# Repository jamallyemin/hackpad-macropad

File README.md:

# hackpad-macropad :3

very kewl 3-key macropad made for hack club hackpad! 

it's a compact custom macropad featuring a rotary encoder, 0.91" OLED screen, WS2812B RGB LED, and a piezo buzzer for cool noises/audio feedback. everything is powered by the Seeed Studio XIAO RP2040 placed right at the top of the board!

## pics !!

### schematic

### 3d case

### pcb layout

### kicad pcb layout

## features !!
* **Seeed XIAO RP2040:** mounted at the top of the PCB for clean USB-C access.
* **3x MX Switches:** mechanical key switches for your daily macros/shortcuts.
* **EC11 Rotary Encoder:** smooth knob control for volume, scrolling, or custom bindings (with built-in push button!).
* **0.91" I2C OLED Display:** 128x32 screen to show custom animations, status info, or graphics.
* **WS2812B RGB LED:** addressable Neopixel for custom lighting effects.
* **Piezo Buzzer:** self-supplied buzzer for playin chiptunes or audio feedback!

## repo structure

* `/PCB` - KiCad schematic (`.kicad_sch`), PCB layout (`.kicad_pcb`), and project files.
* `/CAD` - 3D model STEP files (`hackpad.step`).
* `/production` - Gerber files (`gerbers.zip`), 3D printable STL files (`Top.stl`, `Bottom.stl`), and production code.
* `/images` - Screenshots and 3D preview renders.
* `/Firmware` - CircuitPython code (`main.py`).

## CAD & case design
The enclosure consists of 2 custom 3D printed parts: `Top.stl` and `Bottom.stl`. Everything fits together neatly to protect the PCB and hold the mechanical switches firmly in place. Designed in CAD and exported to `/CAD/hackpad.step`.

## PCB design
Designed using KiCad! The layout puts the XIAO RP2040 at the top edge of the board to allow seamless USB cable plugging without hitting the case walls. All footprints and traces are verified with zero DRC errors.

## firmware overview
Runs using CircuitPython / MicroPython (`main.py`).
* Encoder controls audio/navigation.
* Switches trigger custom macros.
* OLED and RGB LED render real-time UI/feedback.

## stuff used (BOM)
Here's everything needed to build this hackpad:

- **1x** Seeed Studio XIAO RP2040
- **3x** Mechanical MX Switches
- **1x** EC11 Rotary Encoder
- **1x** 0.91" 128x32 I2C OLED Display
- **1x** WS2812B / Neopixel RGB LED
- **1x** Piezo Buzzer *(Self-supplied / extra part)*
- **1x** 3D Printed Top Case (`Top.stl`)
- **1x** 3D Printed Bottom Case (`Bottom.stl`)

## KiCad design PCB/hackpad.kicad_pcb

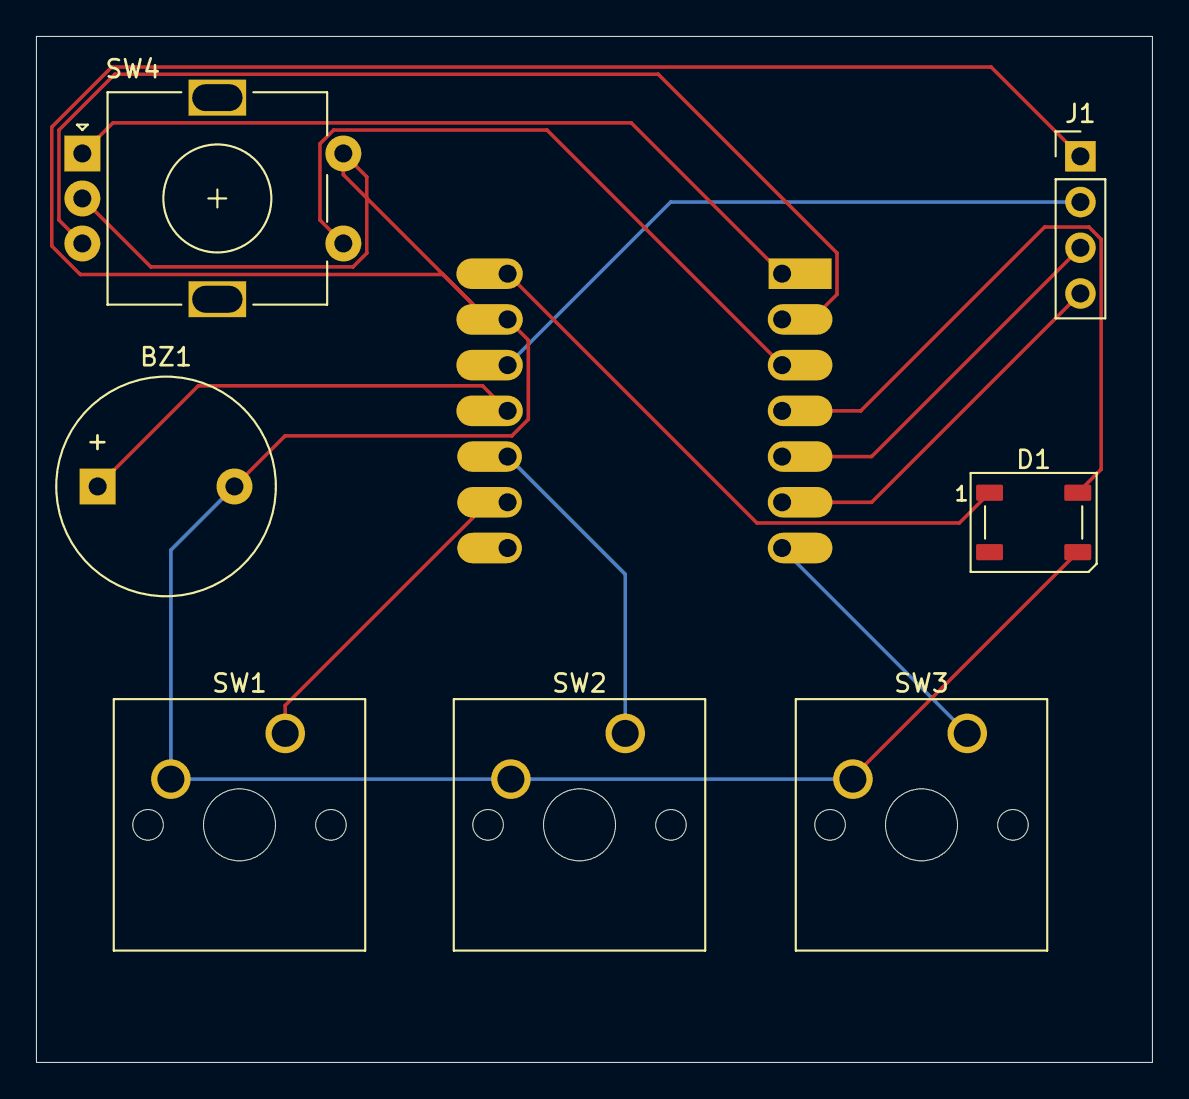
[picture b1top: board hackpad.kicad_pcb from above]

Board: 2 copper layers, 62.0 x 57.0 mm, 8 parts (1 on the bottom side), 13 nets.

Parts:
BZ1: Buzzer; Buzzer_12x9.5RM7.6
D1: WS2812B; LED_WS2812B_PLCC4_5.0x5.0mm_P3.2mm
J1: Conn_01x04_Pin; PinHeader_1x04_P2.54mm_Vertical
SW1, SW2, SW3: SW_Push; SW_Cherry_MX_1.00u_PCB
SW4: RotaryEncoder_Switch; RotaryEncoder_Alps_EC11E-Switch_Vertical_H20mm
U1: MOUDLE-SEEEDUINO-XIAO; XIAO-Generic-Hybrid-14P-2.54-21X17.8MM

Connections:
GND: BZ1.2 (-), D1.3 (VSS), J1.1, SW1.2, SW2.2, SW3.2, SW4.C, SW4.S2, U1.13 (GND)
unnamed: BZ1.1 (+), U1.11 (PA6_A10_D10_MOSI)
unnamed: D1.4 (DIN), U1.4 (PA11_A3_D3)
unnamed: D1.1 (VDD), U1.14 (5V)
unnamed: J1.2, U1.12 (3V3)
unnamed: J1.3, U1.5 (PA8_A4_D4_SDA)
unnamed: J1.4, U1.6 (PA9_A5_D5_SCL)
unnamed: SW4.A, U1.1 (PA02_A0_D0)
unnamed: SW4.B, U1.2 (PA4_A1_D1)
unnamed: SW2.1, U1.10 (PA5_A9_D9_MISO)
unnamed: SW1.1, U1.9 (PA7_A8_D8_SCK)
unnamed: SW4.S1, U1.3 (PA10_A2_D2)
unnamed: SW3.1, U1.7 (PB08_A6_D6_TX)
